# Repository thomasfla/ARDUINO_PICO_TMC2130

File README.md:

# ARDUINO_PICO_TMC2130
Control 3 TMC2130 stepper driver via USB comands (TMX2130 + RP2350 / RP2040)

This is configured to control stepper motors of a bambulab A1 mini.

## Hardware:

* 3x SilentStepStick - TMC2130 Stepper Motor Driver
* 1x Raspberry pi Pico2 dev board

## USB Protocol:

The board will be seen as a virtual COM port.

Send target position, max velocity and max acceleration for all axis (in step, step/s, step/s2)

`X 2000 1000 2000\n`
`Y 500 1000 2000\n` etc..

The driver will send at a chosen period the motor position and velocity:
`X 9030 0 Y 4340 0 Z 0 0`

You can update the target position on the fly. This is usefull for reactive control given other feedback inputs.

## Homing

The code includes a soft homing sequence that as been tuned for Bambulab A1 mini.
This uses stallGuard feature of the tmc2130 drivers.

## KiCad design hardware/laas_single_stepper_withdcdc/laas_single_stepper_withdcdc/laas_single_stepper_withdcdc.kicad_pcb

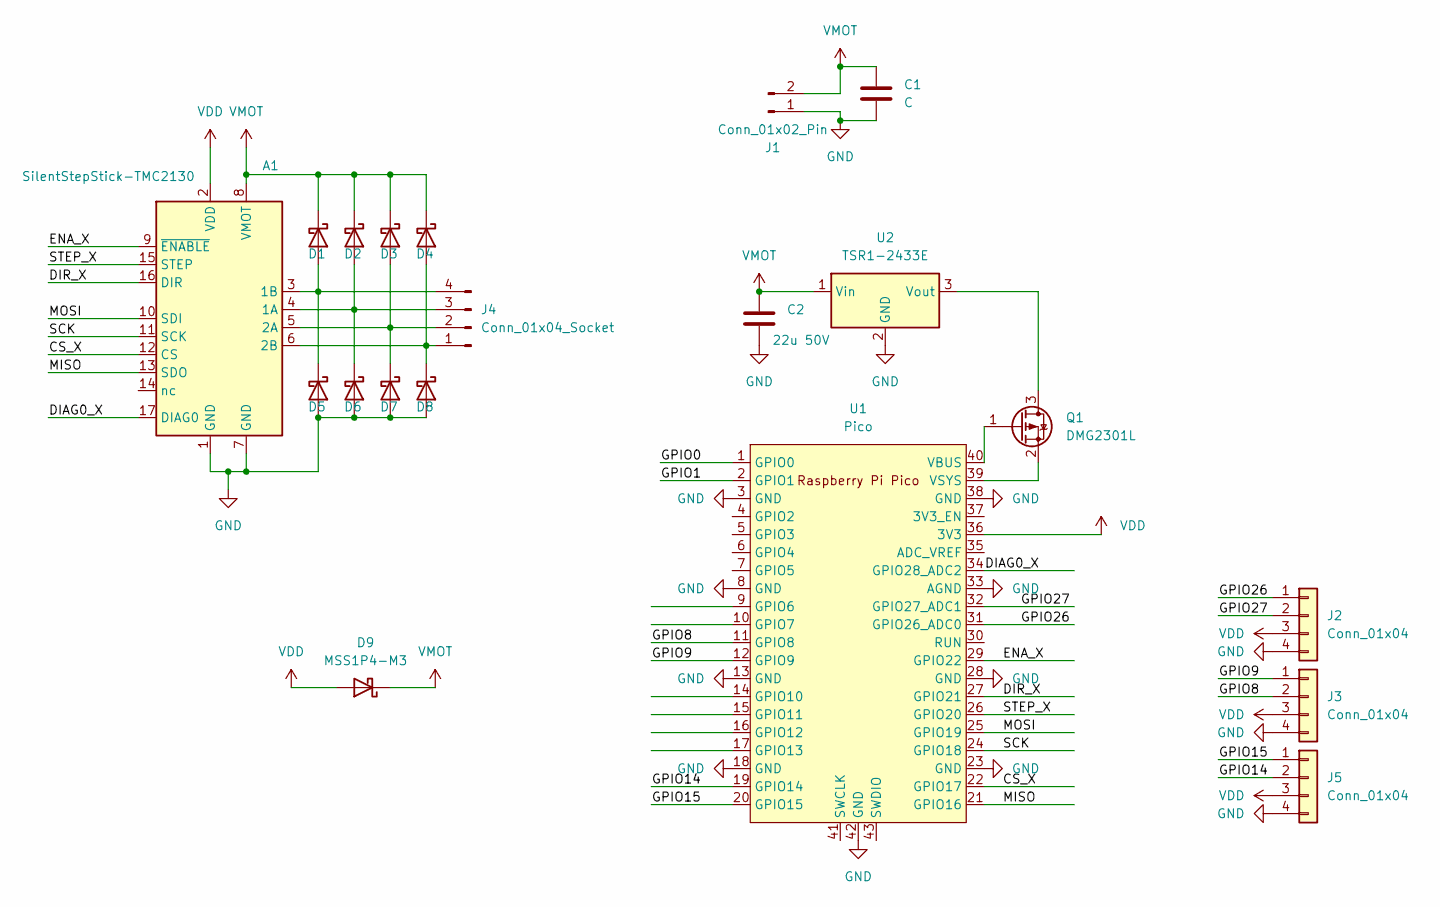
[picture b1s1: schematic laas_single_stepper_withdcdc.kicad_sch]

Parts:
A1: SilentStepStick-TMC2130; Pololu_Breakout-16_15.2x20.3mm
C1: C; C_1210_3225Metric
C2: 22u 50V; C_1210_3225Metric
D1, D2, D3, D4, D5, D6, D7, D8, D9: MSS1P4-M3; D_MicroSMP_AK
J1: Conn_01x02_Pin; AMASS_XT30PW-M_1x02_P2.50mm_Horizontal
J2, J3, J5: Conn_01x04; NS-Tech_Grove_1x04_P2mm_Vertical
J4: Conn_01x04_Socket; JST_XH_S4B-XH-A_1x04_P2.50mm_Horizontal
Q1: DMG2301L; SOT-23
U1: Pico; RPi_Pico_SMD_TH
U2: TSR1-2433E; Converter_DCDC_TRACO_TSR1-xxxxE_THT

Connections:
/CS_X: A1.12 (CS), U1.22 (GPIO17)
/DIAG0_X: A1.17 (DIAG0), U1.34 (GPIO28_ADC2)
/DIR_X: A1.16 (DIR), U1.27 (GPIO21)
/ENA_X: A1.9 (~ENABLE), U1.29 (GPIO22)
/GPIO0: U1.1 (GPIO0)
/GPIO1: U1.2 (GPIO1)
/GPIO8: J3.2, U1.11 (GPIO8)
/GPIO9: J3.1, U1.12 (GPIO9)
/GPIO14: J5.2, U1.19 (GPIO14)
/GPIO15: J5.1, U1.20 (GPIO15)
/GPIO26: J2.1, U1.31 (GPIO26_ADC0)
/GPIO27: J2.2, U1.32 (GPIO27_ADC1)
/MISO: A1.13 (SDO), U1.21 (GPIO16)
/MOSI: A1.10 (SDI), U1.25 (GPIO19)
/SCK: A1.11 (SCK), U1.24 (GPIO18)
/STEP_X: A1.15 (STEP), U1.26 (GPIO20)
GND: A1.1 (GND), A1.7 (GND), C1.2, C2.2, D5.2 (A), D6.2 (A), D7.2 (A), D8.2 (A), J1.1, J2.4, J3.4, J5.4, U1.3 (GND), U1.8 (GND), U1.13 (GND), U1.18 (GND), U1.23 (GND), U1.28 (GND), U1.33 (AGND), U1.38 (GND), U1.42 (GND), U2.2 (GND)
unnamed: A1.4 (1A), D2.2 (A), D6.1 (K), J4.3
unnamed: A1.3 (1B), D1.2 (A), D5.1 (K), J4.4
unnamed: A1.5 (2A), D3.2 (A), D7.1 (K), J4.2
unnamed: A1.6 (2B), D4.2 (A), D8.1 (K), J4.1
unnamed: Q1.3 (D), U2.3 (Vout)
unnamed: Q1.1 (G), U1.40 (VBUS)
unnamed: Q1.2 (S), U1.39 (VSYS)
VDD: A1.2 (VDD), D9.2 (A), J2.3, J3.3, J5.3, U1.36 (3V3)
VMOT: A1.8 (VMOT), C1.1, C2.1, D1.1 (K), D2.1 (K), D3.1 (K), D4.1 (K), D9.1 (K), J1.2, U2.1 (Vin)

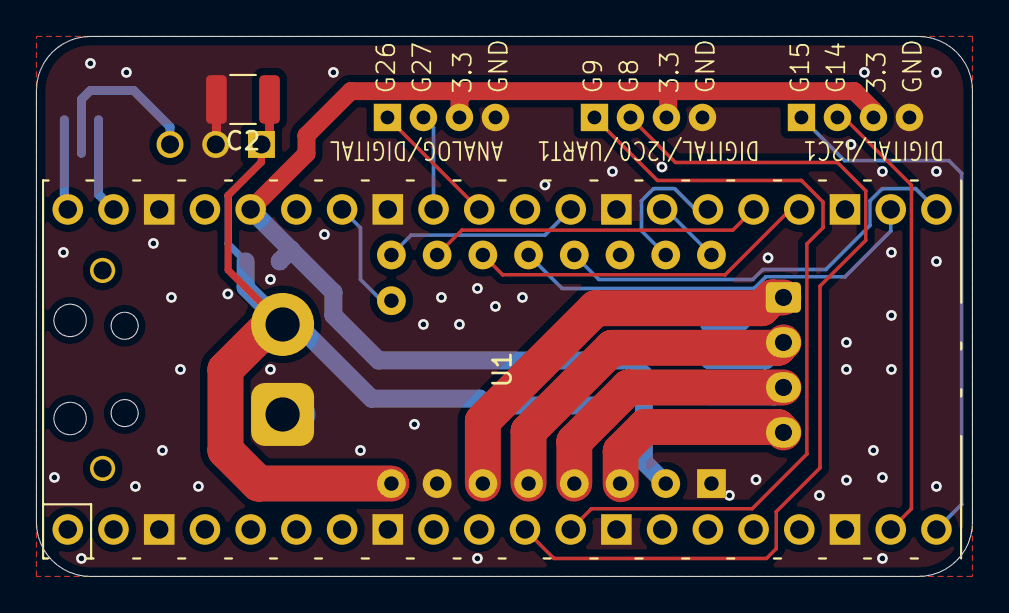
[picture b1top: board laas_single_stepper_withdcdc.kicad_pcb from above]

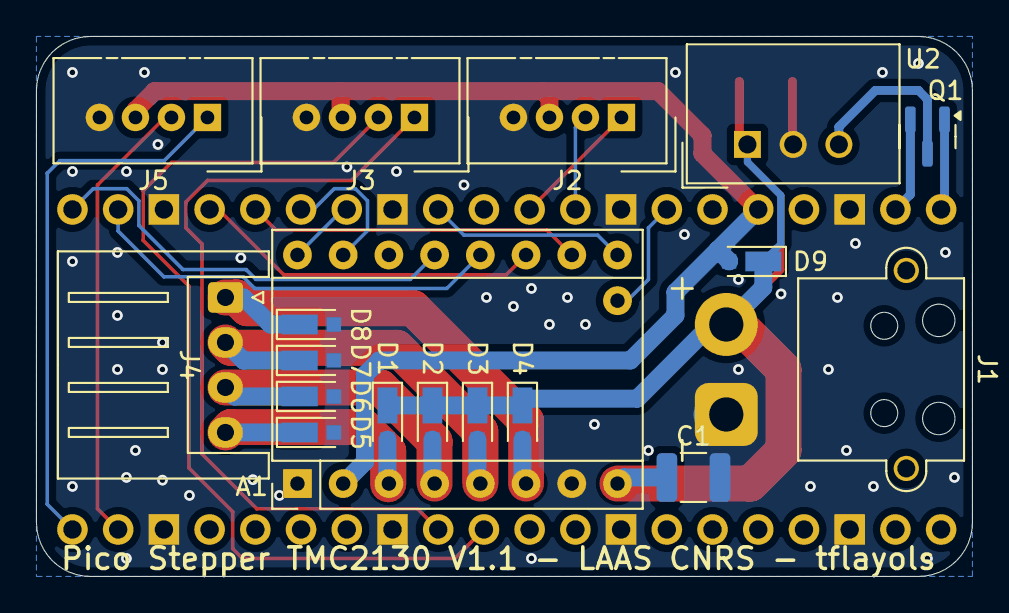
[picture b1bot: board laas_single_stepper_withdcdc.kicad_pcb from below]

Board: 2 copper layers, 52.0 x 30.0 mm, 20 parts (18 on the bottom side), 24 nets.

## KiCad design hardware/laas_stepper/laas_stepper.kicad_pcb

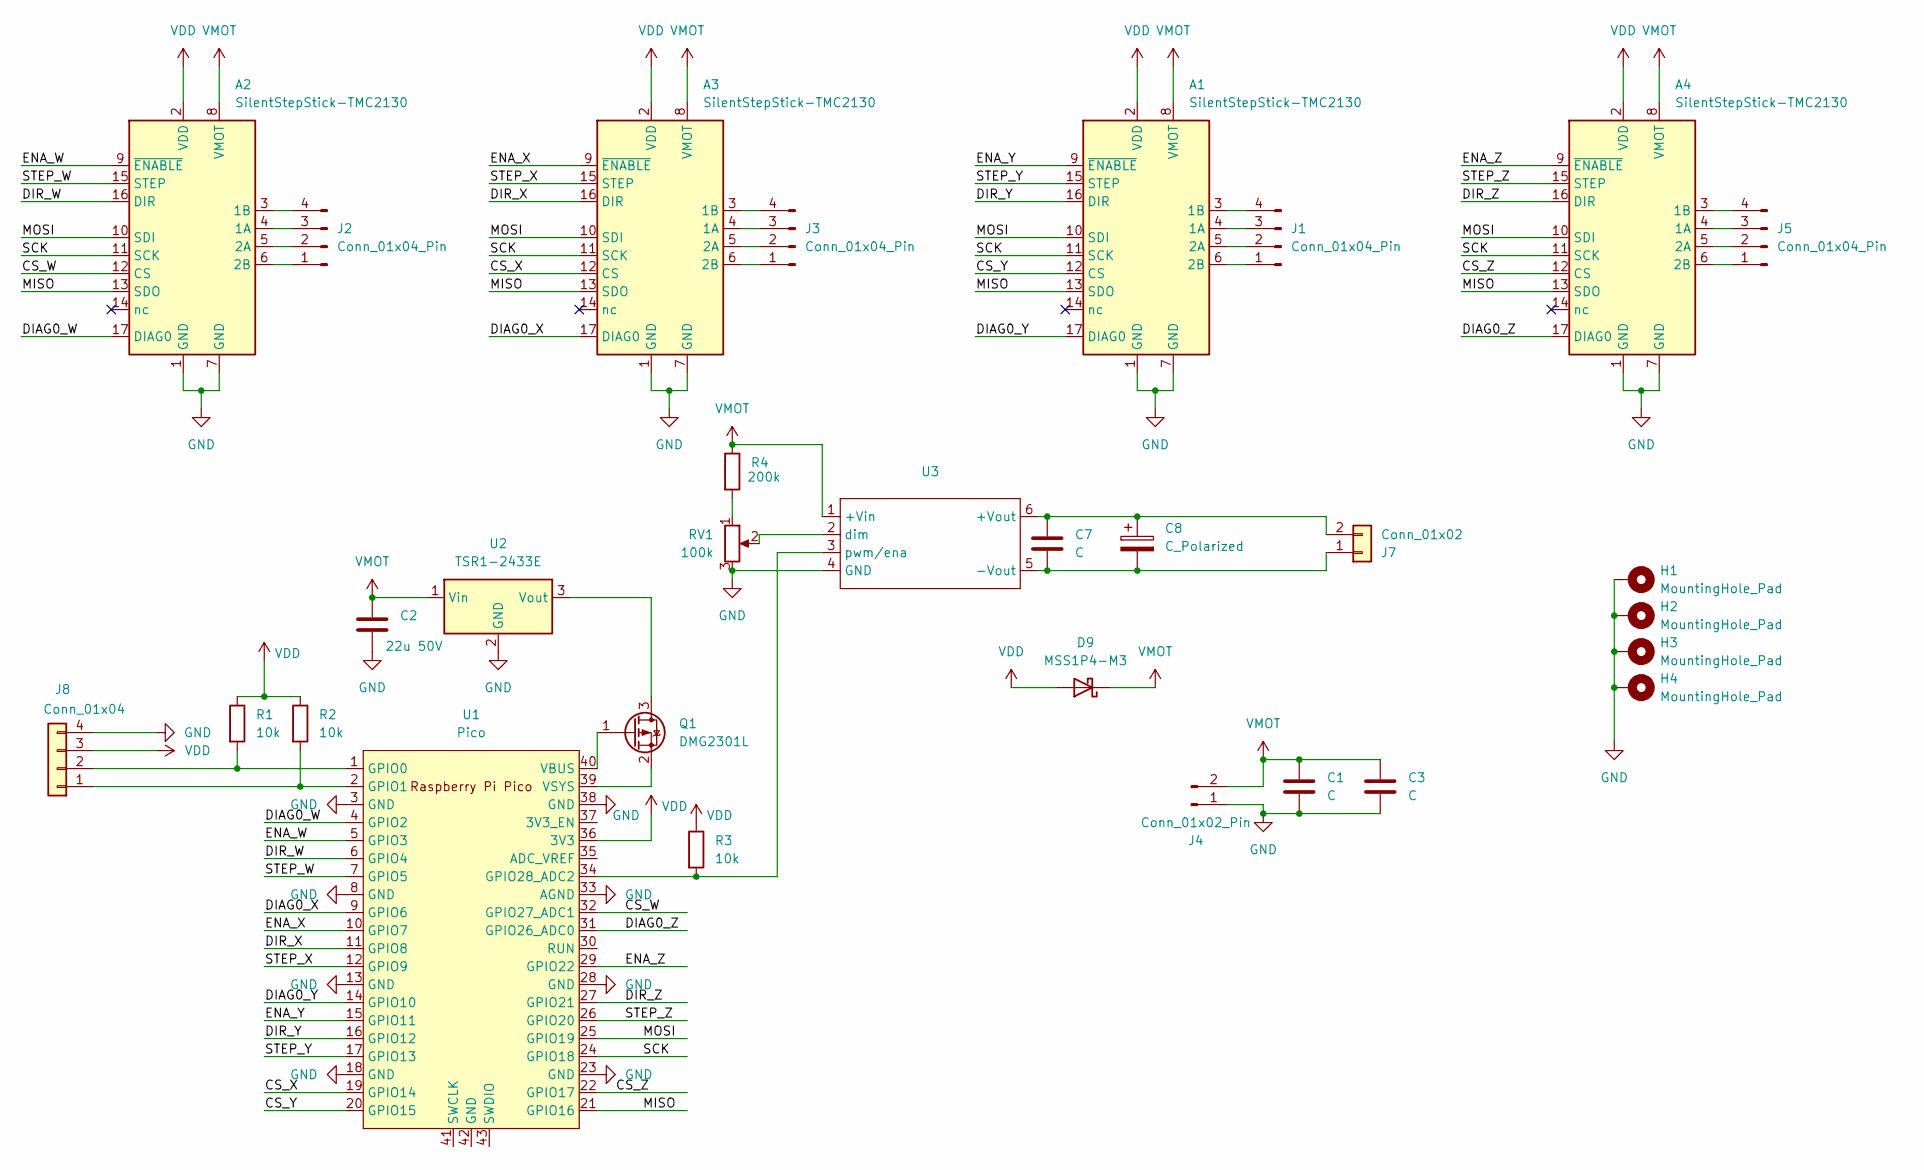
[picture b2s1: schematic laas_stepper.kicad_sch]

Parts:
A1, A2, A3, A4: SilentStepStick-TMC2130; Pololu_Breakout-16_15.2x20.3mm
C1, C3, C7: C; C_1210_3225Metric
C2: 22u 50V; C_1210_3225Metric
C8: C_Polarized; CP_Radial_D8.0mm_P3.80mm
D9: MSS1P4-M3; D_MicroSMP_AK
H1, H2, H3, H4: MountingHole_Pad; MountingHole_2.5mm_Pad_TopBottom
J1, J2, J3, J5: Conn_01x04_Pin; JST_XA_B04B-XASK-1_1x04_P2.50mm_Vertical
J4: Conn_01x02_Pin; AMASS_XT30PW-M_1x02_P2.50mm_Horizontal
J7: Conn_01x02; JST_XH_B2B-XH-A_1x02_P2.50mm_Vertical
J8: Conn_01x04; NS-Tech_Grove_1x04_P2mm_Vertical
Q1: DMG2301L; SOT-23
R1, R2, R3: 10k; R_0805_2012Metric
R4: 200k; R_0805_2012Metric
RV1: 100k; Potentiometer_Bourns_3296W_Vertical
U1: Pico; RaspberryPi_Pico_Common_Unspecified
U2: TSR1-2433E; Converter_DCDC_TRACO_TSR1-xxxxE_THT
U3: RCD-24_PL

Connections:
/CS_W: A2.12 (CS), U1.32 (GPIO27_ADC1)
/CS_X: A3.12 (CS), U1.19 (GPIO14)
/CS_Y: A1.12 (CS), U1.20 (GPIO15)
/CS_Z: A4.12 (CS), U1.22 (GPIO17)
/DIAG0_W: A2.17 (DIAG0), U1.4 (GPIO2)
/DIAG0_X: A3.17 (DIAG0), U1.9 (GPIO6)
/DIAG0_Y: A1.17 (DIAG0), U1.14 (GPIO10)
/DIAG0_Z: A4.17 (DIAG0), U1.31 (GPIO26_ADC0)
/DIR_W: A2.16 (DIR), U1.6 (GPIO4)
/DIR_X: A3.16 (DIR), U1.11 (GPIO8)
/DIR_Y: A1.16 (DIR), U1.16 (GPIO12)
/DIR_Z: A4.16 (DIR), U1.27 (GPIO21)
/ENA_W: A2.9 (~ENABLE), U1.5 (GPIO3)
/ENA_X: A3.9 (~ENABLE), U1.10 (GPIO7)
/ENA_Y: A1.9 (~ENABLE), U1.15 (GPIO11)
/ENA_Z: A4.9 (~ENABLE), U1.29 (GPIO22)
/MISO: A1.13 (SDO), A2.13 (SDO), A3.13 (SDO), A4.13 (SDO), U1.21 (GPIO16)
/MOSI: A1.10 (SDI), A2.10 (SDI), A3.10 (SDI), A4.10 (SDI), U1.25 (GPIO19)
/SCK: A1.11 (SCK), A2.11 (SCK), A3.11 (SCK), A4.11 (SCK), U1.24 (GPIO18)
/STEP_W: A2.15 (STEP), U1.7 (GPIO5)
/STEP_X: A3.15 (STEP), U1.12 (GPIO9)
/STEP_Y: A1.15 (STEP), U1.17 (GPIO13)
/STEP_Z: A4.15 (STEP), U1.26 (GPIO20)
GND: A1.1 (GND), A1.7 (GND), A2.1 (GND), A2.7 (GND), A3.1 (GND), A3.7 (GND), A4.1 (GND), A4.7 (GND), C1.2, C2.2, C3.2, H1.1, H2.1, H3.1, H4.1, J4.1, J8.4, RV1.3, U1.3 (GND), U1.8 (GND), U1.13 (GND), U1.18 (GND), U1.23 (GND), U1.28 (GND), U1.33 (AGND), U1.38 (GND), U2.2 (GND), U3.4 (GND)
unnamed: A1.4 (1A), J1.3
unnamed: A1.3 (1B), J1.4
unnamed: A1.5 (2A), J1.2
unnamed: A1.6 (2B), J1.1
unnamed: A2.4 (1A), J2.3
unnamed: A2.3 (1B), J2.4
unnamed: A2.5 (2A), J2.2
unnamed: A2.6 (2B), J2.1
unnamed: A3.4 (1A), J3.3
unnamed: A3.3 (1B), J3.4
unnamed: A3.5 (2A), J3.2
unnamed: A3.6 (2B), J3.1
unnamed: A4.4 (1A), J5.3
unnamed: A4.3 (1B), J5.4
unnamed: A4.5 (2A), J5.2
unnamed: A4.6 (2B), J5.1
unnamed: C7.2, C8.2, J7.1, U3.5 (-Vout)
unnamed: C7.1, C8.1, J7.2, U3.6 (+Vout)
unnamed: J8.1, R2.2, U1.2 (GPIO1)
unnamed: J8.2, R1.2, U1.1 (GPIO0)
unnamed: Q1.3 (D), U2.3 (Vout)
unnamed: Q1.1 (G), U1.40 (VBUS)
unnamed: Q1.2 (S), U1.39 (VSYS)
unnamed: R4.2, RV1.1
unnamed: R3.2, U1.34 (GPIO28_ADC2), U3.3 (pwm/ena)
unnamed: RV1.2, U3.2 (dim)
VDD: A1.2 (VDD), A2.2 (VDD), A3.2 (VDD), A4.2 (VDD), D9.2 (A), J8.3, R1.1, R2.1, R3.1, U1.36 (3V3)
VMOT: A1.8 (VMOT), A2.8 (VMOT), A3.8 (VMOT), A4.8 (VMOT), C1.1, C2.1, C3.1, D9.1 (K), J4.2, R4.1, U2.1 (Vin), U3.1 (+Vin)

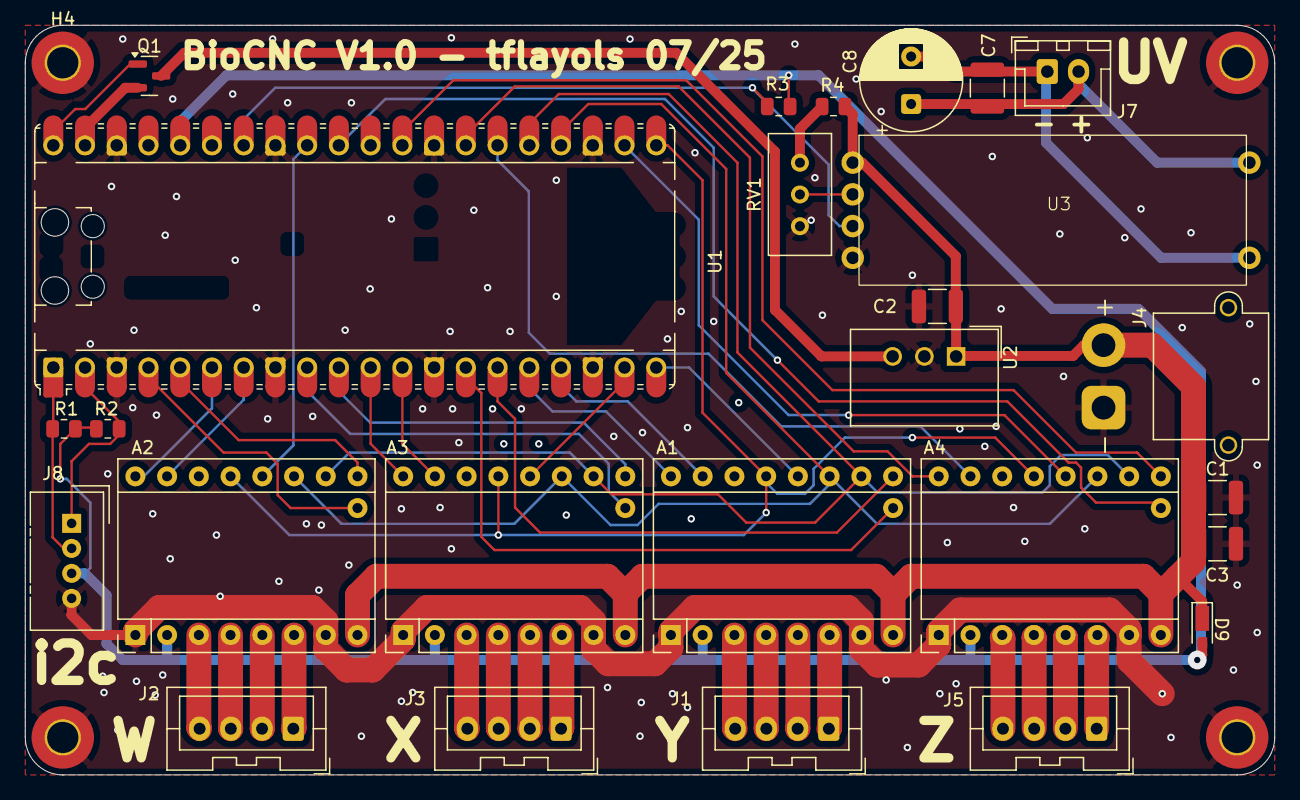
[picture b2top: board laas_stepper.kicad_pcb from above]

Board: 2 copper layers, 100.0 x 60.0 mm, 30 parts (0 on the bottom side), 52 nets.

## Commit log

2025-04-22 add files
2025-04-29 update PCB
2025-07-15 4 axis version, with UV LED controller + GROVE connector; nex single axis with DC DC to make usb power optional, with GROVE connectors
2025-09-08 Adapt firmware to custom board.
